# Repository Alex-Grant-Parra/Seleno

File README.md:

# SELENO telescope client

The client runs on the telescope's Raspberry Pi 5. It joins the telescope to the
ASTRA server ([github.com/Alex-Grant-Parra/ASTRA](https://github.com/Alex-Grant-Parra/ASTRA)), or works
without one. It drives the mount through the ESP32 controller board
(`esp32-firmware/`, protocol in `esp32-firmware/PROTOCOL.md`). It owns the
camera, streams live view, takes and uploads photos, and runs the front
panel's menus.

- [Setting up](#setting-up)
- [What it does](#what-it-does)
- [Configuration](#configuration)
- [Commands the server can send](#commands-the-server-can-send)
- [Tests](#tests)
- [Where things are](#where-things-are)

## Setting up

[QUICK_SETUP.md](QUICK_SETUP.md) has the step-by-step version. In short:

```bash
python -m venv venv
./venv/bin/pip install -r requirements.txt
./venv/bin/python Client.py
```

**First start.** The front panel asks for the device name, the server and the
API key. Choose **Offline** there to use the telescope without a server.
Without a panel, use `config/client_profile.json` or `python Client.py setup`.

**Running as a service.** `deploy/seleno-client.service` is a systemd unit.
The comment at its top says how to install it. It restarts the client if it
fails. The log goes to the journal and to `logs/seleno.log`.

**Plate solving (optional).** This needs ASTAP's command-line solver and a
star database in `~/astap`:
- `astap_cli` for ARM64;
- D05 for telescope-sized fields, W08 for wide lenses.

Without them, everything else works and the solving items stay hidden.

## What it does

### Live view

One thread owns the camera (`core/camera/service.py`), through libgphoto2 in
the same process. If the `gphoto2` Python package is missing, it uses the
`gphoto2` command instead. Nothing kills gphoto2 processes or fights over the
USB port any more.

**Taking a photo during live view.** Live view pauses, the photo is taken,
and live view carries on.

**When live view fails.** It tries again after 1 s, then waits longer each
time, up to 30 s. It never turns itself off. An unplugged camera is noticed,
and found again when it's plugged back in.

**While live view runs.** The camera's auto power-off is switched off, and
put back afterwards.

**What reaches the server is smaller** (`core/camera/stream.py`):

| Quality (`liveview.quality`) | Frame |
|---|---|
| `original` | As the camera sends it |
| `high` | Full size, JPEG quality 80 |
| `medium` (default) | Half size, quality 70: about a ninth of the data |
| `low` | Quarter size, quality 60 |

- **Frame rate:** up to 10 fps while something moves or changes. 2 fps while
  the view is still, skipping frames that look the same, but always one every
  5 s.
- **Slow links:** quality steps down when sends get slow, and back up when
  they're quick again. Before, a send over 2 s dropped the connection and
  restarted the camera.
- **Nobody watching:** once the server reports viewer counts
  (`liveViewViewers`), live view pauses a minute after the last viewer goes,
  and the camera rests. `liveview.idle_stop_min` turns live view off after a
  while with no viewers.
- **Focus mode:** sends a full-resolution crop round the brightest star, and
  measures its HFR (half-flux radius; smaller is sharper).
- **Zoom:** the camera's 5× and 10× live-view zoom, where it has one (Canon).

**Capturing from live view** (`core/camera/recorder.py`):
- a snapshot saves the current frame at once, without the shutter;
- video records every frame into an MJPEG AVI, for stacking Moon and planet
  frames in AutoStakkert or PIPP;
- lossless video (`quality: "lossless"`) records a crop round the planet,
  uncompressed, as SER (`core/camera/ser.py`), for lucky imaging;
- timelapse records one frame every few seconds.

### Photos

- **Photos the server asks for** are saved in `photos/default/` and queued
  for upload (`utils/uploads.py`).
- **How the queue works:**
  - it survives restarts and retries with growing waits;
  - a test shot's JPEG goes ahead of everything; then JPEGs, videos, and
    RAWs following the `upload.raw` setting (`after_jpeg`, `on_request` or
    `never`); `uploadPending("raw", files=..., pairs=...)` sends just some
    held RAWs, first;
  - each file goes on its own, with its meta: where the telescope pointed
    (J2000), `frame_type`, `captured` (UTC with ms), `exposure_s`, `iso`,
    `camera`, `temperature_c` and `focal_mm` when known, and `pair` (the id
    a capture's RAW and JPEG share).
- **Panel photos** (Camera tab) go to `photos/offline/<night>/`, logged in
  `photos.jsonl`. A run can be lights, darks, flats or bias frames. It can
  use bulb exposures and dither between frames (settling `dither_settle_s`
  after each), and darks and bias ask for the cover first. Flats can find
  their own exposure (`exposure_s: "auto"`, `utils/flats.py`): test shots
  until the histogram peak is half full, adjusted between flats.
- **Uploading offline photos:** set the photo owner (your account id) in
  Setup, then use "Upload offline" in the Camera tab.
- **Low disk space:** photos and recordings stop when the Pi has under
  300 MB free.

### Pointing and tracking

Go-tos come from the panel (Scope tab) or the server. The order is:

1. **The Sun guard** (`utils/sun_guard.py`): a warning within 30° of the Sun,
   and a code to enter on the panel within 20°.
2. **Dead zones** (`utils/dead_zones.py`): a target inside one is refused.
3. **The clock, the park and the horizon limit.**
4. **The slew:** the quickest way, over a pole if that's quicker, curving
   round the Sun and the dead zones (`core/hardware/mount.py`).
5. **Tracking**, with the motors run at the right rates.

- **Coordinates:**
  - people and catalogues use J2000;
  - the mount aims at the place of date, corrected for precession (0.37°
    by 2026) and lifted by refraction (`utils/astrometry.py`).
- **The Moon and planets** are worked out on the Pi (`utils/ephemeris.py`),
  within 1.5′ of JPL's DE421. That makes them work offline, in "Go to
  planet" and in the sky view.
- **Tracking rates:**
  - both axes follow the Moon's and planets' own motion;
  - stars use the sidereal rate;
  - lunar, solar and King rates can be chosen, and a custom rate can be set
    in the config;
  - a gentle correction removes any drift.
- **Alignment** (`core/hardware/pointing.py`):
  - each "Align on star" or plate solve is a point, and a pointing model is
    fitted to the points;
  - one point corrects the offsets;
  - three or more find how far the polar axis is out, and say how to move it.
- **Plate solving** (`utils/plate_solve.py`, with ASTAP):
  - solve and sync;
  - centre the target;
  - three-point polar alignment;
  - optional drift checks while tracking.
- **Park:** slews to the park position (the pole, counterweight down, by
  default) round the Sun. Go-tos wait until it's unparked. "Shut down Pi"
  can park first.
- **Southern hemisphere:** picked from the site's latitude. The mount model
  is mirrored and sidereal tracking turns the RA motor the other way.
- **Horizon:**
  - set a minimum altitude, and optionally a profile of trees and roofs;
  - server go-tos below it are refused, and the panel asks;
  - tracking stops when the target sets.
- **Dead zones:** parts of the sky the telescope must never point at: it
  would hit the pier or crush a motor, or look into somebody's window.
  - each is a box in altitude and azimuth (`dead_zones.zones` in the
    config, or `setDeadZones` from the server's Device tab);
  - go-tos into one are refused, from the panel and the server alike;
  - slews curve round them, and are refused when there's no way round;
  - tracking stops when the target drifts into one as the sky turns;
  - raw motor moves are refused into one, and continuous moves stop at
    its edge;
  - moving out of one the telescope is already in is always allowed;
  - zones marked `locked` can't be changed or removed from the server;
  - the server tints them on its star map.
- **Backlash:** extra steps when an axis reverses (`mount.backlash_steps`).
- **Raw motor commands** from the server (the web page's motor panel) are
  guarded (`utils/motor_guard.py`). They're refused past the axis limits,
  towards the Sun or into a dead zone, and continuous moves are stopped
  there.

### Field use

- **Clock** (`utils/clock.py`):
  - go-tos need the right time;
  - offline, with no RTC battery, the Pi's clock is wrong after a power cut;
  - the panel warns, and the time can be set from GPS or typed in
    (Setup > UTC);
  - nothing needs root.
- **GPS:** read from `gpsd` in the background, for the site and the time.
- **Local page** (`core/networking/local_page.py`):
  - turn it on in Setup;
  - it serves live view, photos, snapshots, recording and stop to a phone at
    `http://<pi>:8080/`;
  - it asks for the code shown on the panel.

### Server link

- **Command lanes:** commands run in lanes (`core/networking/websocket.py`),
  so a photo doesn't hold up a slew, and a stop never waits.
- **Replies:** every reply carries the request's id.
- **Live view connection:** opened only while live view is on.
- **Reconnects:** wait 2 s, then longer each time up to a minute, with jitter.

## Configuration

**`config/client_profile.json`:** the device name, server and API key, offline
mode and the site.

**`config/client_config.json`:** everything else, by section. Missing values
take their defaults, and most can be set from the panel.

| Section | Settings |
|---|---|
| `slew_config` | Speeds, gear ratios, centring thresholds |
| `mount` | `ra_axis_limits`, `dec_axis_limits`, `pole_crossing`, `hemisphere` (`auto`/`north`/`south`), `park_axes`, `backlash_steps` |
| `horizon` | `min_alt_deg`, `profile` (`[[az, alt], ...]`), `stop_when_set` |
| `dead_zones` | `zones`: `[{"name", "az": [from, to], "alt": [lowest, highest], "reason": "privacy"/"physical"/"other", "locked"}]`. Azimuth runs clockwise from north; from > to wraps through north, `[0, 360]` is all round |
| `tracking` | `rate` (`sidereal`/`lunar`/`solar`/`king`/`custom`), `custom_arcsec_per_s`, `auto_rate`, `refraction` |
| `liveview` | `quality`, `max_fps`, `still_fps`, `keyframe_s`, `adaptive`, `idle_stop_min`, `viewer_grace_s`, `jpeg_quality` (50-98, full-size frames for focusing; null: the preset), `codec` (`auto`/`jpeg`) |
| `camera` | `backend` (`auto`/`libgphoto2`/`cli`/`fake`), `keep_awake`, `focal_mm` (sent with photos; 0 = unknown) |
| `upload` | `raw` (`after_jpeg`/`on_request`/`never`), `retry_max_s` |
| `photos` | `local_dir`, `owner_id`, `shots`, `kind`, `exposure_s`, `dither` |
| `local_page` | `enabled`, `port` |
| `server` | `raw_motor_commands` (`guarded`/`off`/`unrestricted`), `status_push_s` (default 30; 0 = only on connecting), `allow_remote_update`, `allow_firmware_update` (both off by default) |
| `solver` | `path`, `fov_deg` (0 = learn it), `search_radius_deg`, `timeout_s`, `centre_tolerance_arcmin`, `drift_check_min` |
| `gps` | `enabled` |

`camera.backend: "fake"` gives a made-up camera with a star field, for trying
everything without one.

**`config/runtime_state.json`:** where the telescope points and this session's
alignment. It's kept in memory and written only when something changes.

## Commands the server can send

The server calls these by name: `{"type": "call", "function", "args",
"kwargs", "id"}`. The existing ASTRA web page uses the first group unchanged.
Long jobs (park, plate solves) start in the background and reply at once,
because the server waits only about 3 s. `getJobStatus(name)` says how a job
went.

| Group | Functions |
|---|---|
| Already used by ASTRA | `trackCoordinates(name, ra, dec, mag)`, `stopTracking()`, `getCurrentCoordinates()`, `getCameraChoices()` (now also `current` values and more settings), `setCameraSetting(label, value)`, `capturePhoto(currentid, exposure_s=None, frame_type="light")` (`test`: its JPEG uploads first), `startLiveView(quality=None)`, `stopLiveView()`, `espEnable`, `espSetDirection`, `espSetSpeed`, `espStart`, `espMoveSteps`, `espStop`, `espSetMicrosteps`, `espSetCurrent`, `espSetMode`, `espSetAccel`, `espStatus`, `espStatusAll` |
| Live view | `liveViewViewers(count)`, `getLiveViewStats()`, `setLiveViewOptions(**options)`, `setLiveViewQuality(quality)`, `setLiveViewFocus(on)`, `setCameraZoom(level, x, y)`, `liveViewSnapshot(currentid=None)`, `startRecording(kind, interval_s, quality, currentid, crop_width, crop_height)`, `stopRecording()`, `getRecordingStatus()` |
| Camera and photos | `getCameraStatus()`, `startPhotoSequence(kind, count, exposure_s, interval_s, dither_every, dither_arcmin, dither_settle_s)`, `stopPhotoSequence()`, `getPhotoSequenceStatus()`, `getUploadQueue()`, `uploadPending(kind, files=None, pairs=None)`, `retryFailedUploads()`, `uploadOfflinePhotos(currentid)` |
| Pointing and tracking | `trackObject(name)` (Moon, planets, named stars), `park()`, `unpark()`, `setParkHere()`, `setTrackingRate(rate, custom_arcsec_per_s)`, `dither(arcmin)`, `getAlignment()`, `clearAlignment()`, `solveAndSync(source)`, `centreTarget(source)` (waits for a slew to finish), `polarAlign(step_deg, source)`, `getMountStatus()`, `getJobStatus(name)`, `setClock(utc)`, `setHorizon(min_alt_deg, profile, stop_when_set)`, `getDeadZones()`, `setDeadZones(zones)` (keeps locked zones), `getPlanets()` |
| ESP32 extras | `espSetAuto`, `espDriverStatus`, `espEstop`, `espClearEstop`, `espEstopStatus`, `espInfo`, `espPanelStatus`, `espImuRead`, `espTurnDegrees` |
| The client | `echo`, `getClientStatus()`, `updateClient()`, `updateFirmware()` (the last two only when allowed in config) |

**Two server-side additions would help:**
- **Viewer counts.** Call `liveViewViewers(n)` when people start or stop
  watching `/liveview/<client>`, so the stream can pause with nobody
  watching. Until then it streams whenever live view is on.
- **Status messages.** The client sends a `{"type": "status", ...}` message
  without an id on connecting and every `server.status_push_s` seconds. It
  carries `capabilities` (`capture_frame_type`, `upload_pending_filter`,
  `liveview_jpeg_options`, `dead_zones`), `site`, `dead_zones`
  (`{"zones": [...]}`), the last plate `solve`, and the camera's
  `battery` (percent), `card_free_bytes` and `temperature_c`.

## Tests

```bash
./venv/bin/python -m unittest discover -s tests -t .                                  # the client
./venv/bin/python -m unittest esp32.tests.test_panel_ui esp32.tests.test_interface_pty  # panel and serial link
./venv/bin/ruff check .                                                               # lint
```

No camera, ESP32 or network is needed. The camera tests use a fake camera and
a fake `gphoto2`, and the solver test runs the real ASTAP if it's installed.
`.github/workflows/tests.yml` runs the tests, the lint and both firmware builds.

## Where things are

| Folder | What's in it |
|---|---|
| `Client.py` | Startup |
| `core/camera/` | The camera service and backends, live view stream, JPEG framing, focus, recording |
| `core/hardware/` | Tracking, the mount model and route planner, the pointing model |
| `core/astrometry/` | ASTAP plate solving |
| `core/networking/` | The server links, CSRF, the local page |
| `utils/` | Configuration and state, the front panel (`panel_ui.py`, `panel_menu.py`, `manual_control.py`), the Sun guard, ephemeris, astrometry, clock, GPS, uploads, photos, LEDs |
| `esp32/` | The ESP32 serial interface and bring-up tools |
| `esp32-firmware/` | The controller firmware (PlatformIO) |
| `deploy/` | The systemd unit |
| `tests/` | The client's tests |

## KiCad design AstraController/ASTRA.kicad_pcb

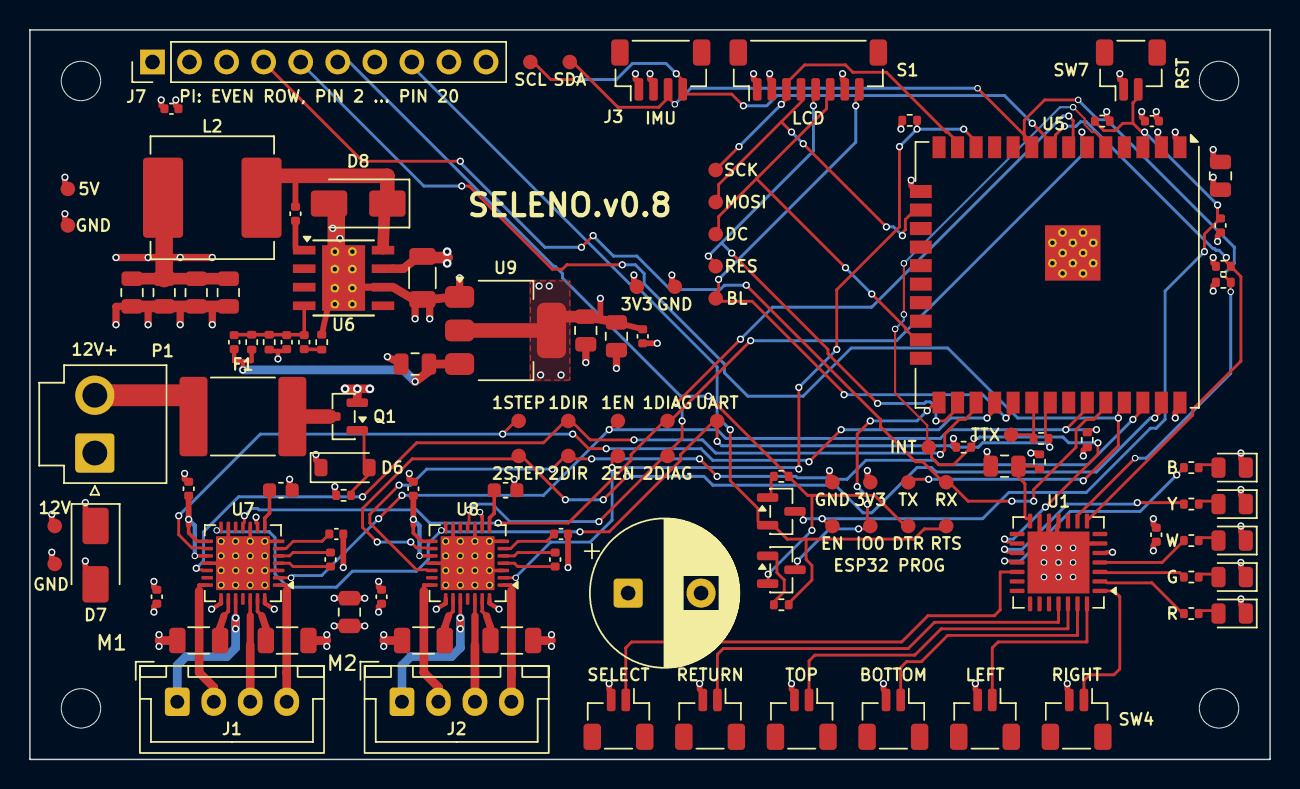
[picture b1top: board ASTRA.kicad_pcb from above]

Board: 4 copper layers, 85.0 x 50.0 mm, 122 parts (0 on the bottom side), 74 nets.

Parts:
C1: 680uF 25V low-ESR; CP_Radial_D10.0mm_P5.00mm
C2, C3, C4, C6, C11, C12, C16, C26, C29, C32, C54: 100nF 50V; C_0402_1005Metric
C7: 1uF 25V; C_0402_1005Metric
C15, C33, C50: 10uF 25V; C_0805_2012Metric
C27, C31: 2.2uF 16V; C_0603_1608Metric
C28, C30: 22nF 50V; C_0402_1005Metric
C35: 10uF 50V; C_1206_3216Metric
C36: 10nF 50V; C_0402_1005Metric
C37, C38, C43, C47, C48, C49, C51: 22uF 25V; C_0805_2012Metric
C52: 1nF 50V; C_0402_1005Metric
C53: 100pF 50V; C_0402_1005Metric
D1: LED_RED; LED_0805_2012Metric
D2: LED_GREEN; LED_0805_2012Metric
D3: LED_WHITE; LED_0805_2012Metric
D4: LED_BLUE; LED_0805_2012Metric
D5: LED_YELLOW; LED_0805_2012Metric
D6: BZT52C10; D_SOD-123
D7: SMAJ15A; D_SMA
D8: SS34; D_SMA
F1: PTC 3A hold 16V+; Fuse_2920_7451Metric
H1, H2, H3, H4: M2.5; MountingHole_2.7mm_M2.5
J1, J2: Nema17; JST_XH_B4B-XH-A_1x04_P2.50mm_Vertical
J3: Conn_01x04; JST_SH_BM04B-SRSS-TB_1x04-1MP_P1.00mm_Vertical
J7: Pi link 1x10; PinHeader_1x10_P2.54mm_Vertical
L2: 15uH; L_Changjiang_FXL0840
P1: 12V-DC; JST_VH_B2P-VH_1x02_P3.96mm_Vertical
Q1: AO3401A; SOT-23
Q2, Q3: MMBT3904; SOT-23
R1, R2, R3, R4, R5, R39: 330R; R_0402_1005Metric
R6, R19, R21, R22, R23, R35, R36, R38: 10kR; R_0402_1005Metric
R7, R8: 4.7kR; R_0402_1005Metric
R16: 1kR; R_0402_1005Metric
R25, R26, R27, R28: 0.15R 0.5W 1%; R_1206_3216Metric
R29: 15kR 1%; R_0402_1005Metric
R30: 4.7kR 1%; R_0402_1005Metric
S1: LCD Display ST7735S; JST_SH_BM08B-SRSS-TB_1x08-1MP_P1.00mm_Vertical
SW1: TOP; JST_SH_BM02B-SRSS-TB_1x02-1MP_P1.00mm_Vertical
SW2: BOTTOM; JST_SH_BM02B-SRSS-TB_1x02-1MP_P1.00mm_Vertical
SW3: LEFT; JST_SH_BM02B-SRSS-TB_1x02-1MP_P1.00mm_Vertical
SW4: RIGHT; JST_SH_BM02B-SRSS-TB_1x02-1MP_P1.00mm_Vertical
SW5: SELECT; JST_SH_BM02B-SRSS-TB_1x02-1MP_P1.00mm_Vertical
SW6: RETURN; JST_SH_BM02B-SRSS-TB_1x02-1MP_P1.00mm_Vertical
SW7: RESET; JST_SH_BM02B-SRSS-TB_1x02-1MP_P1.00mm_Vertical
TP1: +12V; TestPoint_Pad_D1.0mm
TP2, TP4, TP6, TP14: GND; TestPoint_Pad_D1.0mm
TP3: +5V; TestPoint_Pad_D1.0mm
TP5, TP15: +3.3V; TestPoint_Pad_D1.0mm
TP7: SCL; TestPoint_Pad_D1.0mm
TP8: SDA; TestPoint_Pad_D1.0mm
TP9: SCK; TestPoint_Pad_D1.0mm
TP10: MOSI; TestPoint_Pad_D1.0mm
TP11: DC; TestPoint_Pad_D1.0mm
TP12: RES; TestPoint_Pad_D1.0mm
TP13: BL; TestPoint_Pad_D1.0mm
TP16: UART1; TestPoint_Pad_D1.0mm
TP17: UART2; TestPoint_Pad_D1.0mm
TP18: ESP32EN; TestPoint_Pad_D1.0mm
TP19: GPIO0; TestPoint_Pad_D1.0mm
TP20: Pi Link/DTR; TestPoint_Pad_D1.0mm
TP21: Pi Link/RTS; TestPoint_Pad_D1.0mm
TP22: 1STEP; TestPoint_Pad_D1.0mm
TP23: 1DIR; TestPoint_Pad_D1.0mm
TP24: 1EN; TestPoint_Pad_D1.0mm
TP25: T1_DIAG; TestPoint_Pad_D1.0mm
TP26: TMC_UART; TestPoint_Pad_D1.0mm
TP27: 2STEP; TestPoint_Pad_D1.0mm
TP28: 2DIR; TestPoint_Pad_D1.0mm
TP29: 2EN; TestPoint_Pad_D1.0mm
TP30: T2_DIAG; TestPoint_Pad_D1.0mm
TP31: TMC_TX; TestPoint_Pad_D1.0mm
TP33: EXP_INT; TestPoint_Pad_D1.0mm
U1: MCP23017x-x-ML; QFN-28-1EP_6x6mm_P0.65mm_EP4.25x4.25mm
U5: ESP32-WROOM-32UE
U6: TPS5430DDAR; TI_SO-PowerPAD-8_ThermalVias
U7, U8: TMC2209-LA; VQFN-28-1EP_5x5mm_P0.5mm_EP3.7x3.7mm_ThermalVias
U9: AMS1117-3.3; SOT-223-3_TabPin2

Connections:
1DIR: TP23.1, U5.27, U7.19
1EN: R35.2, TP24.1, U5.33, U7.2
1STEP: TP22.1, U5.28, U7.16
2DIR: TP28.1, U5.36, U8.19
2EN: R36.2, TP29.1, U5.12, U8.2
2STEP: TP27.1, U5.37, U8.16
+3.3V: C3.1, C4.1, C6.1, C11.1, C15.1, C16.1, C43.1, C51.1, J3.2, R6.2, R7.1, R8.1, R19.2, R35.1, R36.1, R38.1, S1.2, TP5.1, TP15.1, U1.5, U5.2, U7.15, U7.17, U8.9, U8.15, U8.17, U9.2
+5V: C12.1, C37.1, C38.1, C48.1, C49.1, C50.1, C52.1, J7.1, J7.2, L2.2, R29.1, TP3.1, U9.3
+12V: C1.1, C2.1, C26.2, C29.2, C32.1, C35.1, C47.1, D6.1, D7.1, Q1.2, TP1.1, U6.7, U7.22, U7.28, U8.22, U8.28
/Pi Link/DTR: J7.6, Q2.2, R22.2, TP20.1
/Pi Link/RTS: J7.8, Q3.2, R23.2, TP21.1
/Power/5V_FB: C52.2, C53.1, C54.1, R29.2, R30.1, U6.4
/Power/5V_SW: C36.2, D8.1, L2.1, U6.8
/User Interface/BLUE: R4.2, U1.18
/User Interface/BOTTOM: SW2.1, U1.27
/User Interface/GREEN: R2.2, U1.3
/User Interface/LEFT: SW3.1, U1.28
/User Interface/RED: R1.2, U1.2
/User Interface/RETURN: SW6.1, U1.25
/User Interface/RIGHT: SW4.1, U1.1
/User Interface/SELECT: SW5.1, U1.19
/User Interface/TOP: SW1.1, U1.26
/User Interface/WHITE: R3.2, U1.4
/User Interface/YELLOW: R5.2, U1.17
BL: S1.8, TP13.1, U5.29
DC: S1.6, TP11.1, U5.23
ESP32EN: C7.2, Q3.3, R6.1, SW7.2, TP18.1, U5.3
EXP_INT: R38.2, TP33.1, U1.16, U5.5
GND: C1.2, C2.2, C3.2, C4.2, C6.2, C7.1, C11.2, C12.2, C15.2, C16.2, C27.2, C31.2, C32.2, C33.1, C35.2, C37.2, C38.2, C43.2, C47.2, C48.2, C49.2, C50.2, C51.2, C53.2, D1.1, D2.1, D3.1, D4.1, D5.1, D7.2, D8.2, J3.1, J7.3, J7.7, J7.10, P1.1, R21.2, R25.1, R26.1, R27.1, R28.1, R30.2, R39.2, S1.1, S1.7, SW1.2, SW2.2, SW3.2, SW4.2, SW5.2, SW6.2, SW7.1, TP2.1, TP4.1, TP6.1, TP14.1, U1.6, U1.11, U1.12, U1.13, U1.29, U5.1, U5.15, U5.38, U5.39, U6.6, U6.9, U7.3, U7.7, U7.9, U7.10, U7.13, U7.18, U7.29, U8.3, U8.7, U8.10, U8.13, U8.18, U8.29, U9.1
GPIO0: Q2.3, TP19.1, U5.25
MOSI: S1.4, TP10.1, U5.16
unnamed: C54.2, R39.1
unnamed: D1.2, R1.1
unnamed: D2.2, R2.1
unnamed: D3.2, R3.1
unnamed: D4.2, R4.1
unnamed: D5.2, R5.1
unnamed: D6.2, Q1.1, R21.1
unnamed: F1.2, P1.2
unnamed: J1.1, U7.24
unnamed: J1.2, U7.21
unnamed: J1.3, U7.26
unnamed: J1.4, U7.1
unnamed: J2.1, U8.24
unnamed: J2.2, U8.21
unnamed: J2.3, U8.26
unnamed: J2.4, U8.1
unnamed: F1.1, Q1.3
unnamed: Q2.1, R23.1
unnamed: Q3.1, R22.1
unnamed: C33.2, R19.1, U1.14
unnamed: C36.1, U6.1
unnamed: C27.1, U7.8
unnamed: R25.2, U7.23
unnamed: R26.2, U7.27
unnamed: C28.2, U7.5
unnamed: C28.1, U7.4
unnamed: C26.1, U7.6
unnamed: C31.1, U8.8
unnamed: R27.2, U8.23
unnamed: R28.2, U8.27
unnamed: C30.2, U8.5
unnamed: C30.1, U8.4
unnamed: C29.1, U8.6
RES: S1.5, TP12.1, U5.26
SCK: S1.3, TP9.1, U5.13
SCL: J3.4, R7.2, TP7.1, U1.8, U5.8
SDA: J3.3, R8.2, TP8.1, U1.9, U5.9
T1_DIAG: TP25.1, U5.6, U7.11
T2_DIAG: TP30.1, U5.7, U8.11
TMC_TX: R16.2, TP31.1, U5.30
TMC_UART: R16.1, TP26.1, U5.31, U7.14, U8.14
UART1: J7.5, TP16.1, U5.35
UART2: J7.4, TP17.1, U5.34

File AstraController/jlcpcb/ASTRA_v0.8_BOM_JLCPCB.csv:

"Comment","Designator","Footprint","JLCPCB Part #"
"100nF 50V X7R","C2,C3,C4,C6,C11,C12,C16,C26,C29,C32,C54","0402","C307331"
"22nF 50V X7R","C28,C30","0402","C1532"
"10nF 50V X7R","C36","0402","C15195"
"1nF 50V X7R","C52","0402","C1523"
"100pF 50V C0G","C53","0402","C1546"
"1uF 25V X5R","C7","0402","C52923"
"2.2uF 16V X5R","C27,C31","0603","C23630"
"10uF 25V X5R","C15,C33,C50","0805","C15850"
"22uF 25V X5R","C37,C38,C43,C47,C48,C49,C51","0805","C45783"
"10uF 50V X5R","C35","1206","C13585"
"10k 1%","R6,R19,R21,R22,R23,R35,R36,R38","0402","C25744"
"330R 1%","R1,R2,R3,R4,R5,R39","0402","C25104"
"4.7k 1%","R7,R8,R30","0402","C25900"
"15k 1%","R29","0402","C25756"
"1k 1%","R16","0402","C11702"
"BZT52C10","D6","SOD-123","C19077408"
"SMAJ15A","D7","SMA(DO-214AC)","C19077535"
"SS34","D8","SMA(DO-214AC)","C8678"
"2920L300/15DR","F1","2920","C207089"
"FXL0840-150-M 15uH","L2","SMD 8.8x8.2mm","C5298372"
"AO3401A","Q1","SOT-23","C15127"
"MMBT3904","Q2,Q3","SOT-23","C20526"
"MCP23017-E/ML","U1","QFN-28-EP(6x6)","C639770"
"TPS5430DDAR","U6","SOIC-8-EP","C9864"
"TMC2209-LA-T","U7,U8","QFN-28-EP(5x5)","C2150710"
"AMS1117-3.3","U9","SOT-223","C6186"

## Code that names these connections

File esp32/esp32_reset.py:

"""Reset the ESP32, or put it in its ROM bootloader, from the Pi.

Both wiring options drive the same esptool-style transistor pair (Q2/Q3 on
the SELENO v0.8 board, the equivalent pair on a dev kit). Levels below are
the electrical levels on the two control lines, as in the hardware report's
truth table ("Auto-program pair"):

	DTR RTS
	 0   0   runs normally (Pi power-on default)
	 1   1   runs normally
	 1   0   EN low: held in reset
	 0   1   GPIO0 low: download mode if EN rises now

* v0.8 board: Pi GPIO18 is "DTR", GPIO23 is "RTS" (J7 pins 6 and 8).
* Dev kit on USB: the USB-serial chip's DTR/RTS outputs, which are active
  low, so pyserial's ``dtr=True`` means electrical 0.
"""
from __future__ import annotations

import time
from typing import Optional, Protocol

GPIO_DTR = 18
GPIO_RTS = 23

_RESET_HOLD_S = 0.10
_BOOT_STRAP_S = 0.10


class ResetLines(Protocol):
	def set_levels(self, dtr: int, rts: int) -> None: ...
	def release(self) -> None: ...


class SerialResetLines:
	"""DTR/RTS of an open pyserial port (dev kit on USB)."""

	def __init__(self, ser) -> None:
		self.ser = ser

	def set_levels(self, dtr: int, rts: int) -> None:
		# The chip's outputs are inverted: asserted (True) = electrical 0.
		self.ser.dtr = not bool(dtr)
		self.ser.rts = not bool(rts)

	def release(self) -> None:
		self.set_levels(1, 1)


class GpioResetLines:
	"""Pi GPIO18/GPIO23 wired through J7 (SELENO v0.8 board).

	Needs gpiozero with a working pin factory (lgpio on a Pi 5):
	``pip install gpiozero lgpio`` in the venv.
	"""

	def __init__(self, dtr_pin: int = GPIO_DTR, rts_pin: int = GPIO_RTS) -> None:
		try:
			from gpiozero import DigitalOutputDevice
		except ImportError as exc:  # pragma: no cover - depends on the Pi image
			raise RuntimeError(
				"GPIO reset needs gpiozero (and lgpio on a Pi 5): pip install gpiozero lgpio"
			) from exc
		# Both start low: the ESP32 keeps running while the pins are claimed.
		self._dtr = DigitalOutputDevice(dtr_pin, initial_value=False)
		self._rts = DigitalOutputDevice(rts_pin, initial_value=False)

	def set_levels(self, dtr: int, rts: int) -> None:
		self._dtr.value = 1 if dtr else 0
		self._rts.value = 1 if rts else 0

	def release(self) -> None:
		# Back to inputs; the Pi's pull-downs keep both low, so it keeps running.
		self.set_levels(0, 0)
		self._dtr.close()
		self._rts.close()


def reset_to_app(lines: ResetLines) -> None:
	"""Pulse EN with GPIO0 high: a normal reboot into the firmware."""
	lines.set_levels(1, 0)
	time.sleep(_RESET_HOLD_S)
	lines.set_levels(0, 0)


def enter_bootloader(lines: ResetLines) -> None:
	"""Release EN while GPIO0 is low, so the ROM waits for esptool."""
	lines.set_levels(1, 0)
	time.sleep(_RESET_HOLD_S)
	lines.set_levels(0, 1)
	time.sleep(_BOOT_STRAP_S)
	lines.set_levels(0, 0)


def lines_for(transport: str, ser=None) -> ResetLines:
	"""The reset lines for a transport ("usb" or "gpio_uart")."""
	if transport == "usb":
		if ser is None:
			raise ValueError("USB reset needs the open serial port")
		return SerialResetLines(ser)
	if transport == "gpio_uart":
		return GpioResetLines()
	raise ValueError(f"No reset lines for transport {transport!r}")


def reset_esp32(transport: str, ser=None, bootloader: bool = False) -> None:
	lines: Optional[ResetLines] = None
	try:
		lines = lines_for(transport, ser)
		if bootloader:
			enter_bootloader(lines)
		else:
			reset_to_app(lines)
	finally:
		if lines is not None and isinstance(lines, GpioResetLines):
			lines.release()

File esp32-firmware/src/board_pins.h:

// SELENO v0.8 ESP32 pin map.
// Every number comes from the KiCad netlist, as listed in
// "SELENO Controller v0.8 Hardware Report.txt", section "Board pin header".
#pragma once

#include <cstdint>

// Host link: UART0 -> J7 -> Pi GPIO14/15 (nets UART1 = TX, UART2 = RX)
constexpr int PIN_HOST_TX = 1;
constexpr int PIN_HOST_RX = 3;

// TMC2209 single-wire UART: U7 address 0, U8 address 1
constexpr int PIN_TMC_TX = 18;  // through R16 1k
constexpr int PIN_TMC_RX = 19;  // TMC_UART bus

// Motor 1 (RA): U7 -> J1
constexpr int PIN_M1_STEP = 17;
constexpr int PIN_M1_DIR  = 16;
constexpr int PIN_M1_EN   = 21;  // active low, R35 pull-up keeps it off
constexpr int PIN_M1_DIAG = 34;  // input only

// Motor 2 (DEC): U8 -> J2
constexpr int PIN_M2_STEP = 23;
constexpr int PIN_M2_DIR  = 22;
constexpr int PIN_M2_EN   = 27;  // active low, R36 pull-up keeps it off
constexpr int PIN_M2_DIAG = 35;  // input only

// I2C: MCP23017 at 0x20, IMU board on J3. Not the Arduino default 21/22,
// which are motor pins here.
constexpr int PIN_SDA     = 33;
constexpr int PIN_SCL     = 32;
constexpr int PIN_EXP_INT = 39;  // MCP23017 INTA, active low, R38 pull-up

// LCD: ST7735S on S1, CS tied low on the connector
constexpr int PIN_LCD_SCK  = 14;
constexpr int PIN_LCD_MOSI = 13;
constexpr int PIN_LCD_DC   = 15;
constexpr int PIN_LCD_RST  = 4;
constexpr int PIN_LCD_BL   = 5;
constexpr int PIN_LCD_CS   = -1;

// Unconnected on v0.8 (strap, low at boot). It is the onboard LED on the
// dev kit, so it backs the "board" LED channel. Driving it after boot is safe.
constexpr int PIN_BOARD_LED = 2;

// Auxiliary host UART (devkit builds only, SELENO_AUX_HOST_UART=1). Both pins
// are spare on v0.8. Wire Pi GPIO14 (TXD) -> IO26 and Pi GPIO15 (RXD) <- IO25.
constexpr int PIN_AUX_HOST_RX = 26;
constexpr int PIN_AUX_HOST_TX = 25;

constexpr uint8_t MCP23017_ADDR = 0x20;
constexpr uint8_t BNO08X_ADDR   = 0x4A;  // 0x4B if the IMU board's SA0 is high
constexpr uint8_t BNO08X_ADDR_ALT = 0x4B;
constexpr float   TMC_RSENSE    = 0.15f;  // ohms (R25-R28)

// MCP23017 port bits (report, "Buttons and LEDs: U1").
// Port A
constexpr uint8_t MCP_A_YELLOW = 0;
constexpr uint8_t MCP_A_BLUE   = 1;
constexpr uint8_t MCP_A_SELECT = 2;
// Port B
constexpr uint8_t MCP_B_RETURN = 0;
constexpr uint8_t MCP_B_TOP    = 1;
constexpr uint8_t MCP_B_BOTTOM = 2;
constexpr uint8_t MCP_B_LEFT   = 3;
constexpr uint8_t MCP_B_RIGHT  = 4;
constexpr uint8_t MCP_B_RED    = 5;
constexpr uint8_t MCP_B_GREEN  = 6;
constexpr uint8_t MCP_B_WHITE  = 7;
